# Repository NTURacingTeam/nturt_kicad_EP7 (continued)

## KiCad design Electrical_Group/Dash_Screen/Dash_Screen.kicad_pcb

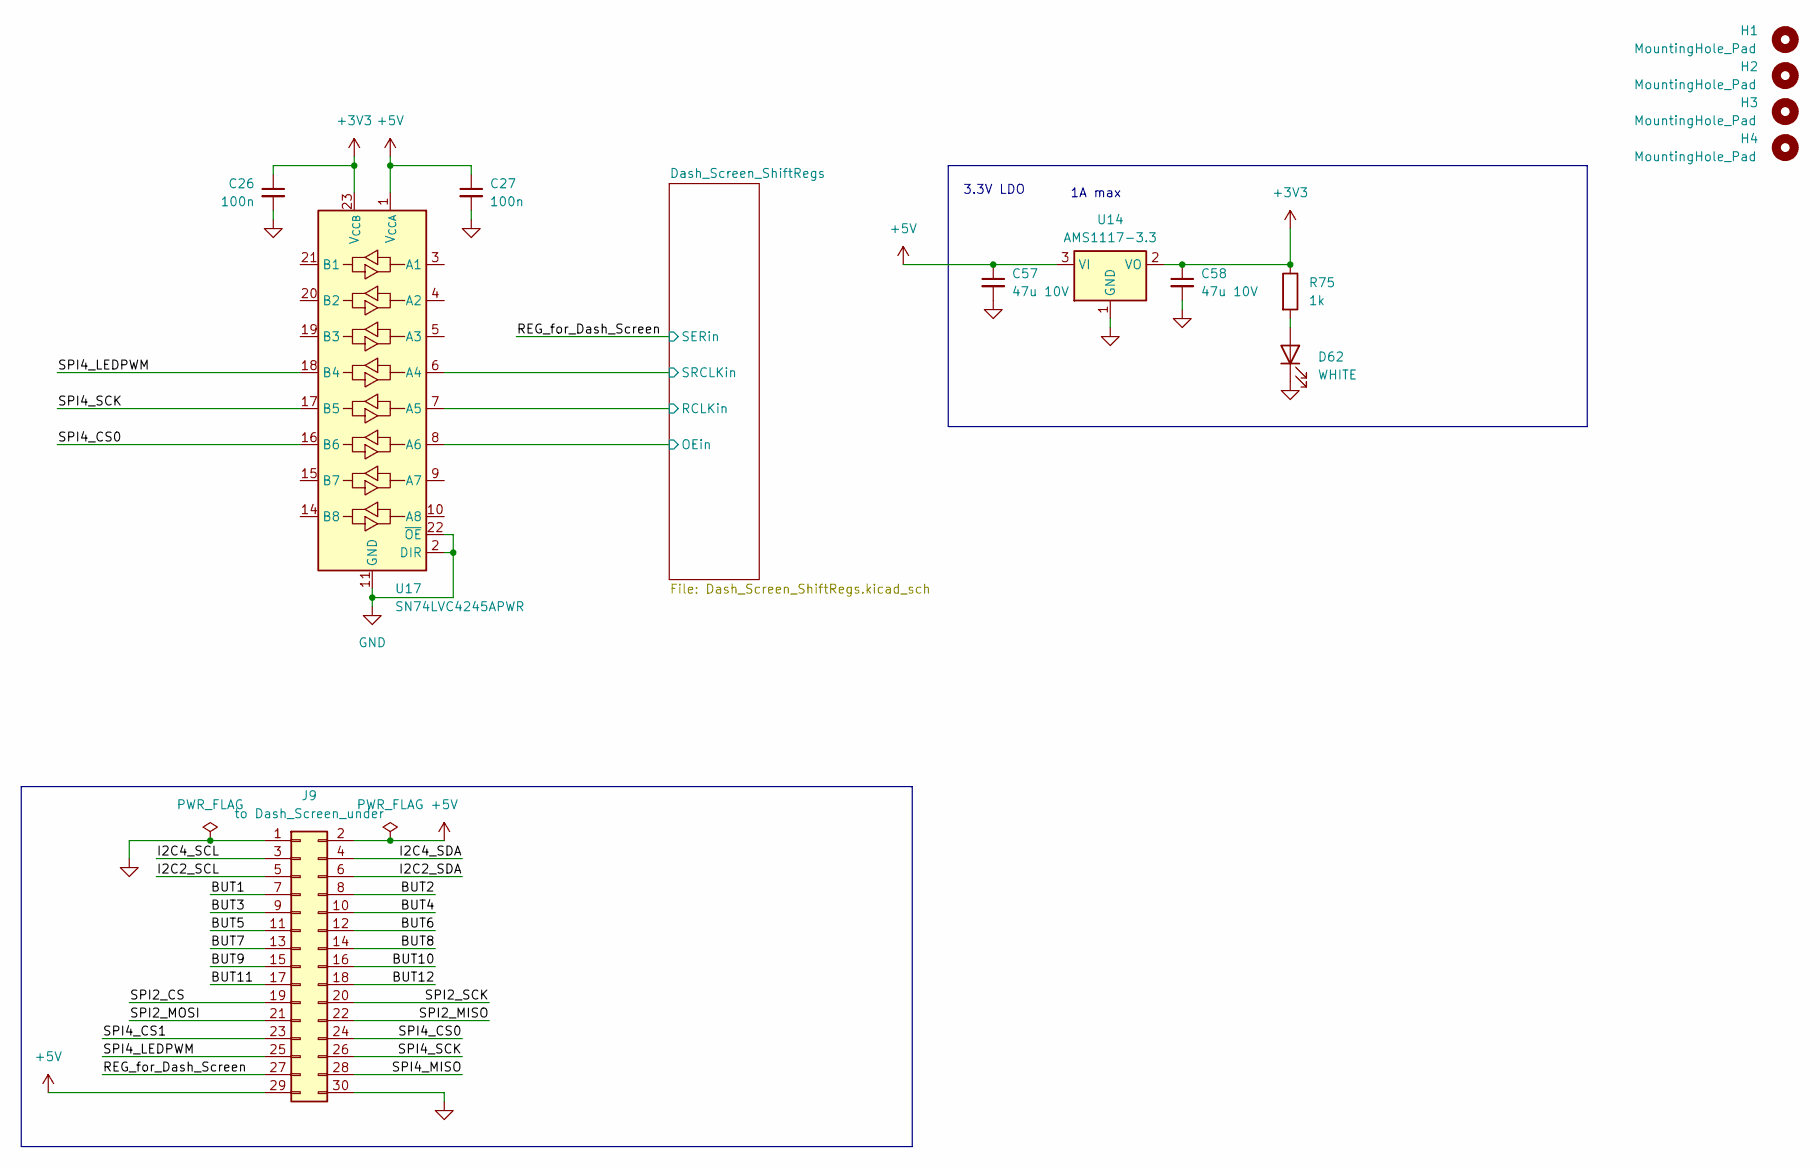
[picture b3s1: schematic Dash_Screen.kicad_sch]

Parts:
C26, C27: 100n; C_0603_1608Metric
C57, C58: 47u 10V; C_1206_3216Metric
D62: WHITE; LED_0603_1608Metric
H1, H2, H3, H4: MountingHole_Pad; MountingHole_3.2mm_M3
J9: to Dash_Screen_under; PinSocket_2x15_P2.00mm_Vertical_SMD
R75: 1k; R_0603_1608Metric
U14: AMS1117-3.3; SOT-223-3_TabPin2
U17: SN74LVC4245APWR; TSSOP-24_4.4x7.8mm_P0.65mm

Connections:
+3V3: C26.1, C58.1, R75.1, U14.2 (VO), U17.23 (V_{CCB}), U17.24 (V_{CCB})
+5V: C27.1, C57.1, J9.2, J9.29, U14.3 (VI), U17.1 (V_{CCA}); also elsewhere on the board
/BUT1: J9.7
/BUT2: J9.8
/BUT3: J9.9
/BUT4: J9.10
/BUT5: J9.11
/BUT6: J9.12
/BUT7: J9.13
/BUT8: J9.14
/BUT9: J9.15
/BUT10: J9.16
/BUT11: J9.17
/BUT12: J9.18
/Dash_Screen_ShiftRegs/OE: U17.8 (A6); also elsewhere on the board
/Dash_Screen_ShiftRegs/RCLK: U17.7 (A5); also elsewhere on the board
/Dash_Screen_ShiftRegs/SRCLK: U17.6 (A4); also elsewhere on the board
/I2C2_SCL: J9.5
/I2C2_SDA: J9.6
/I2C4_SCL: J9.3
/I2C4_SDA: J9.4
/REG_for_Dash_Screen: J9.27; also elsewhere on the board
/SPI2_CS: J9.19
/SPI2_MISO: J9.22
/SPI2_MOSI: J9.21
/SPI2_SCK: J9.20
/SPI4_CS0: J9.24, U17.16 (B6)
/SPI4_CS1: J9.23
/SPI4_LEDPWM: J9.25, U17.18 (B4)
/SPI4_MISO: J9.28
/SPI4_SCK: J9.26, U17.17 (B5)
GND: C26.2, C27.2, C57.2, C58.2, D62.1 (K), J9.1, J9.30, U14.1 (GND), U17.2 (DIR), U17.11 (GND), U17.12 (GND), U17.13 (GND), U17.22 (~OE); also elsewhere on the board
unnamed: D62.2 (A), R75.2

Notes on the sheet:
3.3V LDO
1A max

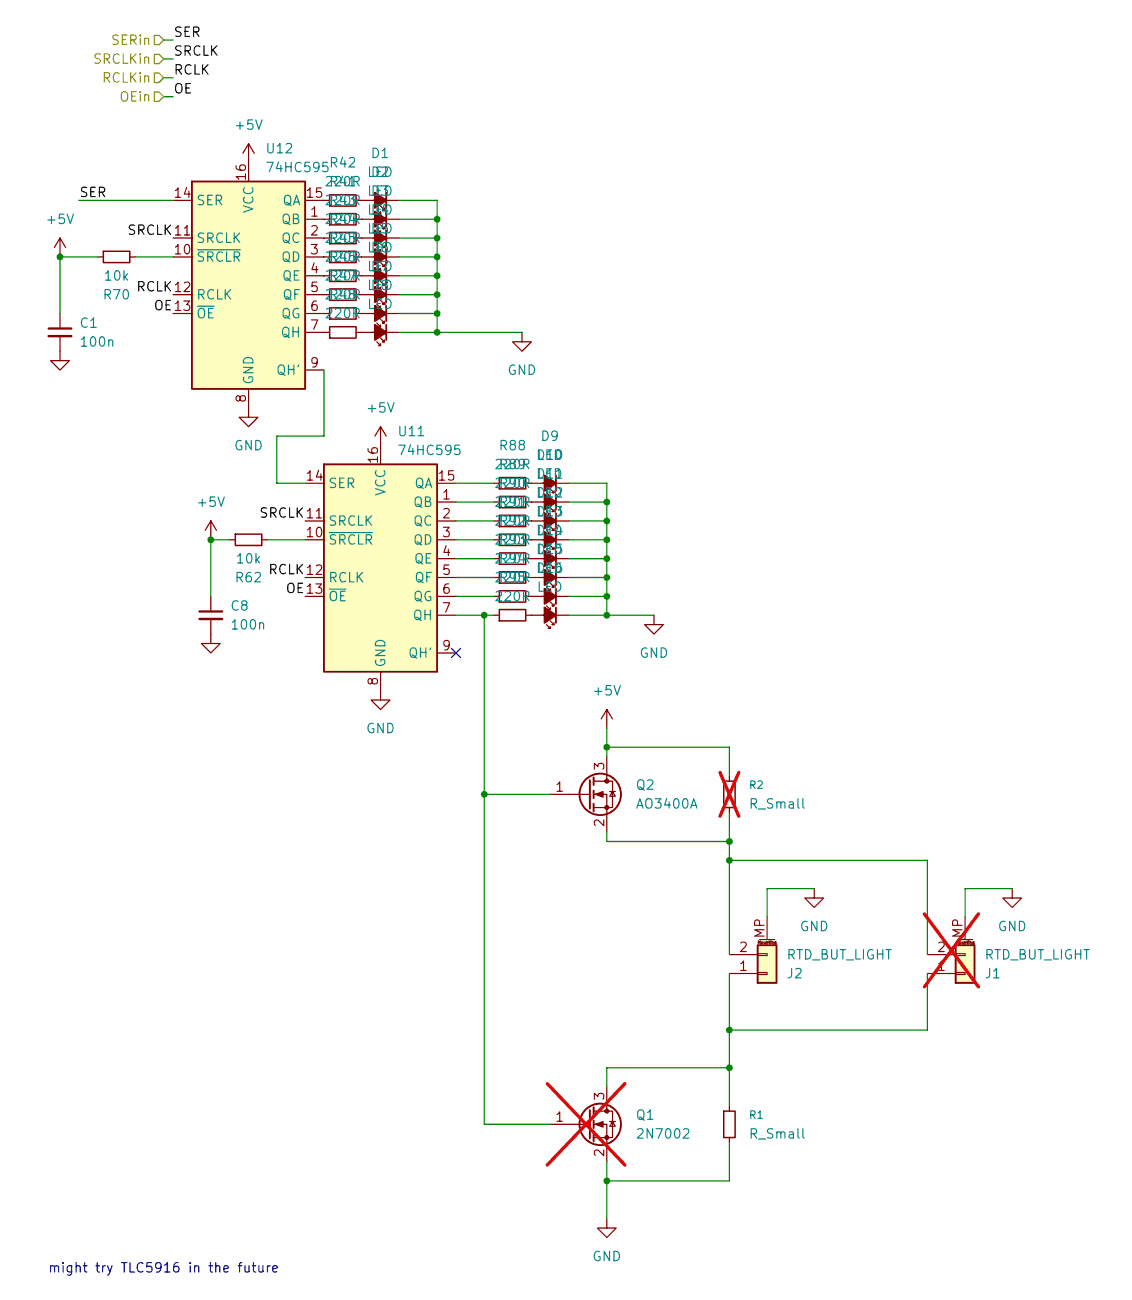
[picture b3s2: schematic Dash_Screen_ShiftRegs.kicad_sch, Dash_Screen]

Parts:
C1, C8: 100n; C_0603_1608Metric
D1, D2, D3, D4, D5, D6, D7, D8, D9, D10, D11, D12, D13, D14, D15, D16: LED; LED_PLCC_2835_Handsoldering
J1: RTD_BUT_LIGHT; JST_PH_S2B-PH-SM4-TB_1x02-1MP_P2.00mm_Horizontal; not fitted
J2: RTD_BUT_LIGHT; JST_PH_S2B-PH-SM4-TB_1x02-1MP_P2.00mm_Horizontal
Q1: 2N7002; SOT-23; not fitted
Q2: AO3400A; SOT-23
R1: R_Small; R_0805_2012Metric_Pad1.20x1.40mm_HandSolder
R2: R_Small; R_0805_2012Metric_Pad1.20x1.40mm_HandSolder; not fitted
R41, R42, R43, R44, R45, R46, R47, R48, R88, R89, R90, R91, R92, R93, R94, R95: 220R; R_0603_1608Metric_Pad0.98x0.95mm_HandSolder
R62, R70: 10k; R_0603_1608Metric
U11, U12: 74HC595; SOIC-16_3.9x9.9mm_P1.27mm

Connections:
+5V: C1.1, C8.1, Q2.3 (D), R2.1, R62.1, R70.1, U11.16 (VCC), U12.16 (VCC); also elsewhere on the board
/Dash_Screen_ShiftRegs/OE: U11.13 (~OE), U12.13 (~OE); also elsewhere on the board
/Dash_Screen_ShiftRegs/RCLK: U11.12 (RCLK), U12.12 (RCLK); also elsewhere on the board
/Dash_Screen_ShiftRegs/SRCLK: U11.11 (SRCLK), U12.11 (SRCLK); also elsewhere on the board
/REG_for_Dash_Screen: U12.14 (SER); also elsewhere on the board
GND: C1.2, C8.2, D1.1 (K), D2.1 (K), D3.1 (K), D4.1 (K), D5.1 (K), D6.1 (K), D7.1 (K), D8.1 (K), D9.1 (K), D10.1 (K), D11.1 (K), D12.1 (K), D13.1 (K), D14.1 (K), D15.1 (K), D16.1 (K), J1.MP (MountPin), J2.MP (MountPin), Q1.2 (S), R1.2, U11.8 (GND), U12.8 (GND); also elsewhere on the board
unnamed: D1.2 (A), R42.2
unnamed: D2.2 (A), R41.2
unnamed: D3.2 (A), R43.2
unnamed: D4.2 (A), R44.2
unnamed: D5.2 (A), R45.2
unnamed: D6.2 (A), R46.2
unnamed: D7.2 (A), R47.2
unnamed: D8.2 (A), R48.2
unnamed: D9.2 (A), R88.2
unnamed: D10.2 (A), R89.2
unnamed: D11.2 (A), R90.2
unnamed: D12.2 (A), R91.2
unnamed: D13.2 (A), R92.2
unnamed: D14.2 (A), R93.2
unnamed: D15.2 (A), R94.2
unnamed: D16.2 (A), R95.2
unnamed: J1.1, J2.1, Q1.3 (D), R1.1
unnamed: J1.2, J2.2, Q2.2 (S), R2.2
unnamed: Q1.1 (G), Q2.1 (G), R95.1, U11.7 (QH)
unnamed: R88.1, U11.15 (QA)
unnamed: R89.1, U11.1 (QB)
unnamed: R90.1, U11.2 (QC)
unnamed: R91.1, U11.3 (QD)
unnamed: R92.1, U11.4 (QE)
unnamed: R93.1, U11.5 (QF)
unnamed: R94.1, U11.6 (QG)
unnamed: U11.14 (SER), U12.9 (QH')
unnamed: R62.2, U11.10 (~SRCLR)
unnamed: R42.1, U12.15 (QA)
unnamed: R41.1, U12.1 (QB)
unnamed: R43.1, U12.2 (QC)
unnamed: R44.1, U12.3 (QD)
unnamed: R45.1, U12.4 (QE)
unnamed: R46.1, U12.5 (QF)
unnamed: R47.1, U12.6 (QG)
unnamed: R48.1, U12.7 (QH)
unnamed: R70.2, U12.10 (~SRCLR)

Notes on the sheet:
might try TLC5916 in the future

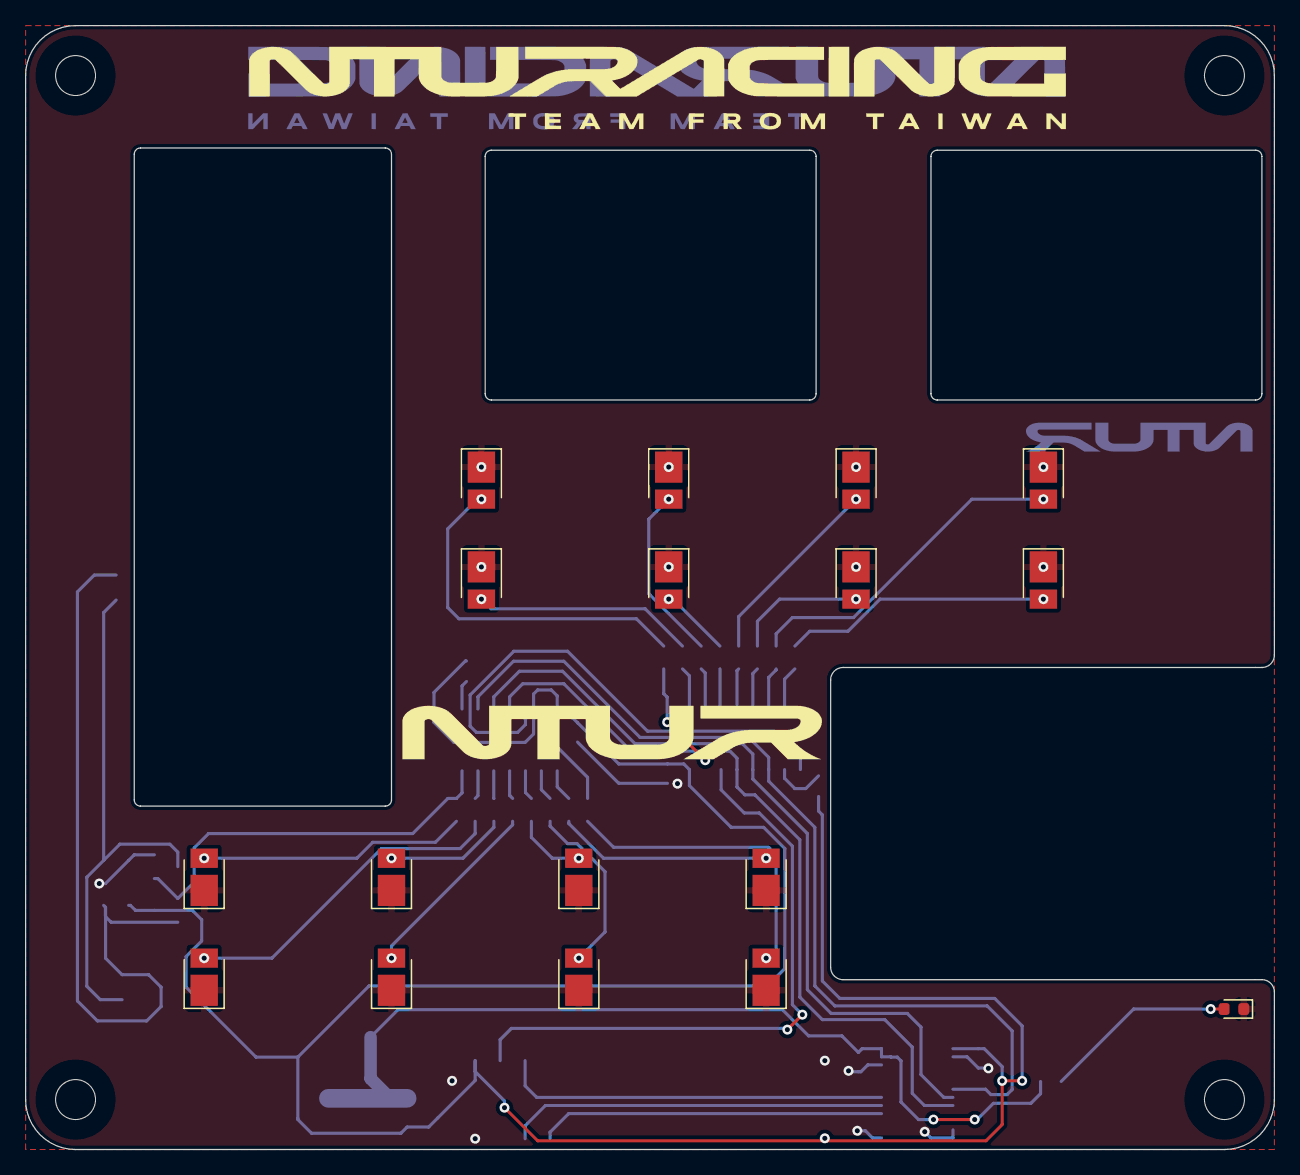
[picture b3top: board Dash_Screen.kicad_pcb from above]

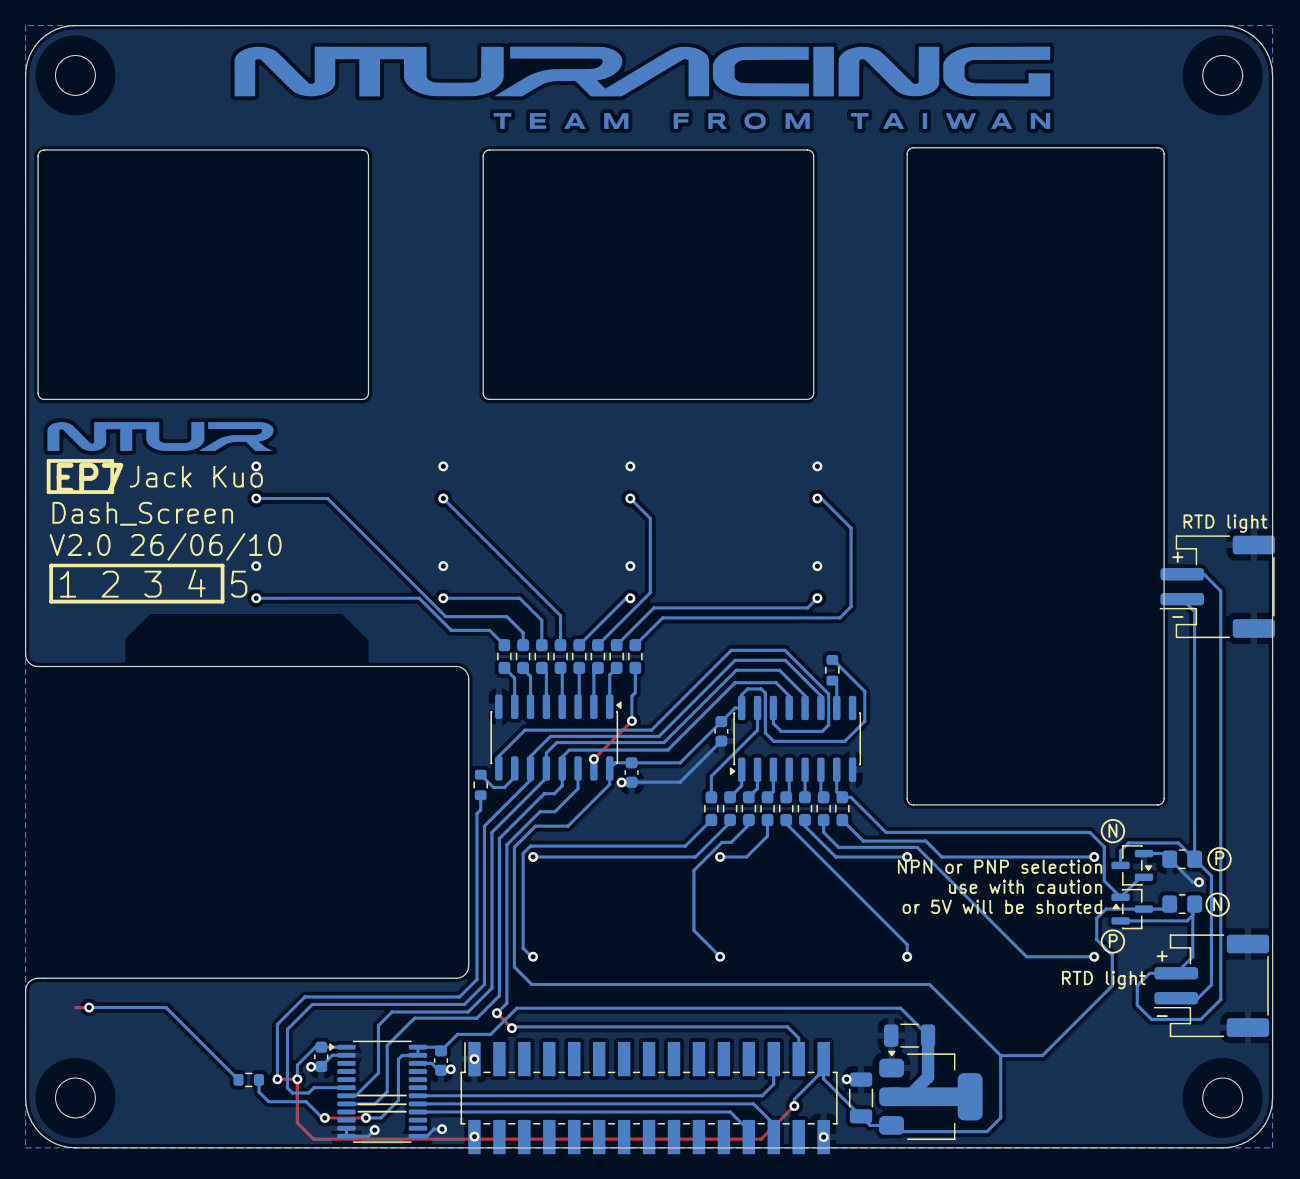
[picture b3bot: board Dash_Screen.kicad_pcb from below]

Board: 2 copper layers, 100.0 x 90.0 mm, 57 parts (36 on the bottom side), 48 nets.

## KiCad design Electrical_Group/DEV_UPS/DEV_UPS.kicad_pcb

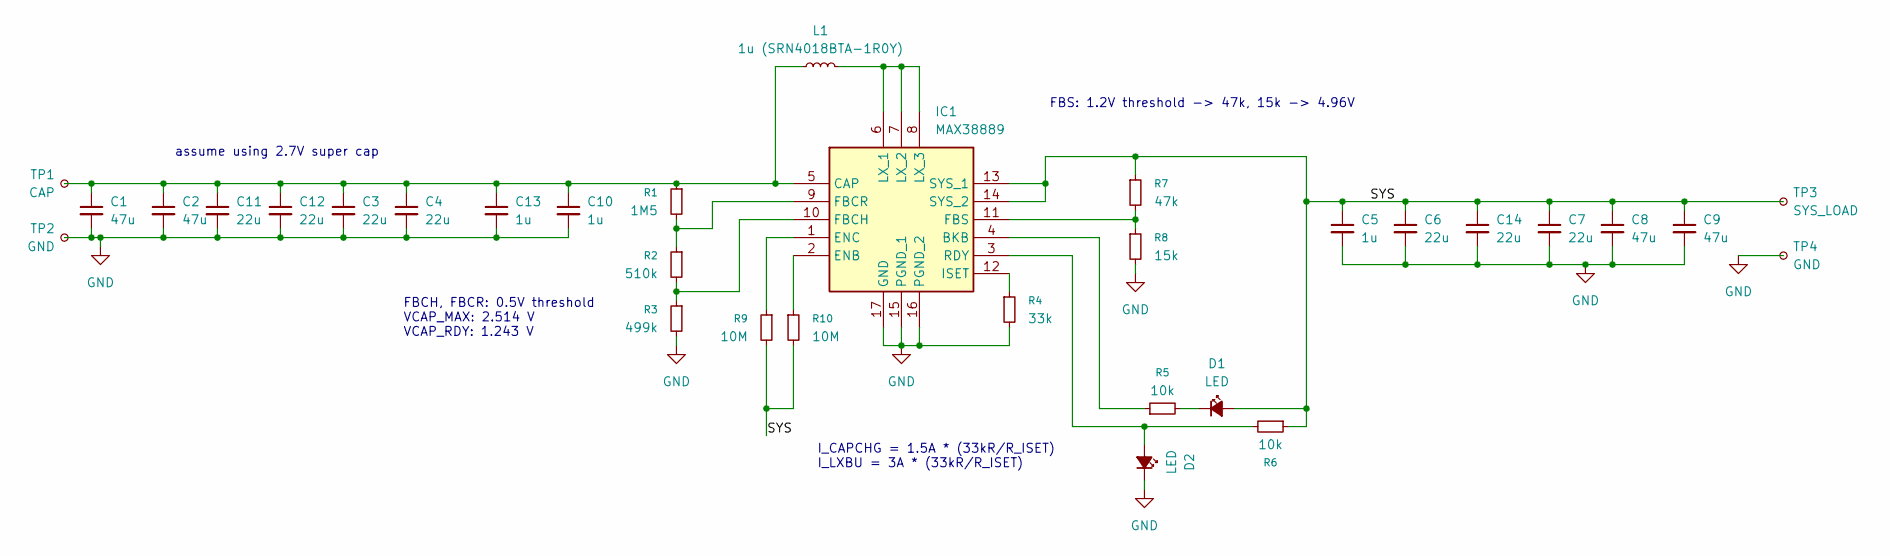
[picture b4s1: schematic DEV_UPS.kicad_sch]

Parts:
C1, C2, C8, C9: 47u; C_1206_3216Metric_Pad1.33x1.80mm_HandSolder
C3, C4, C6, C7, C11, C12, C14: 22u; C_0805_2012Metric_Pad1.18x1.45mm_HandSolder
C5, C10, C13: 1u; C_0603_1608Metric_Pad1.08x0.95mm_HandSolder
D1, D2: LED; LED_0603_1608Metric_Pad1.05x0.95mm_HandSolder
IC1: MAX38889; TQFN-16-1EP_3x3mm_P0.5mm_EP1.6x1.6mm; Mouser Part Number 700-MAX38889AATE+
L1: 1u (SRN4018BTA-1R0Y); L_Bourns-SRN4018
R1: 1M5; R_0603_1608Metric_Pad0.98x0.95mm_HandSolder
R2: 510k; R_0603_1608Metric_Pad0.98x0.95mm_HandSolder
R3: 499k; R_0603_1608Metric_Pad0.98x0.95mm_HandSolder
R4: 33k; R_0603_1608Metric_Pad0.98x0.95mm_HandSolder
R5, R6: 10k; R_0603_1608Metric_Pad0.98x0.95mm_HandSolder
R7: 47k; R_0603_1608Metric_Pad0.98x0.95mm_HandSolder
R8: 15k; R_0603_1608Metric_Pad0.98x0.95mm_HandSolder
R9, R10: 10M; R_0603_1608Metric_Pad0.98x0.95mm_HandSolder
TP1: CAP; edge_pad_1.4mm_0.7mm
TP2, TP4: GND; edge_pad_1.4mm_0.7mm
TP3: SYS_LOAD; edge_pad_1.4mm_0.7mm

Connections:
/SYS: C5.1, C6.1, C7.1, C8.1, C9.1, C14.1, D1.2 (A), IC1.13 (SYS_1), IC1.14 (SYS_2), R6.1, R7.1, R9.2, R10.2, TP3.1
GND: C1.2, C2.2, C3.2, C4.2, C5.2, C6.2, C7.2, C8.2, C9.2, C10.2, C11.2, C12.2, C13.2, C14.2, D2.1 (K), IC1.15 (PGND_1), IC1.16 (PGND_2), IC1.17 (GND), R3.2, R4.2, R8.2, TP2.1, TP4.1
unnamed: D1.1 (K), R5.2
unnamed: D2.2 (A), IC1.3 (RDY), R6.2
unnamed: IC1.4 (BKB), R5.1
unnamed: C1.1, C2.1, C3.1, C4.1, C10.1, C11.1, C12.1, C13.1, IC1.5 (CAP), L1.1, R1.1, TP1.1
unnamed: IC1.2 (ENB), R10.1
unnamed: IC1.1 (ENC), R9.1
unnamed: IC1.10 (FBCH), R2.2, R3.1
unnamed: IC1.9 (FBCR), R1.2, R2.1
unnamed: IC1.11 (FBS), R7.2, R8.1
unnamed: IC1.12 (ISET), R4.1
unnamed: IC1.6 (LX_1), IC1.7 (LX_2), IC1.8 (LX_3), L1.2

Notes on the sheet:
I_CAPCHG = 1.5A * (33kR/R_ISET) I_LXBU = 3A * (33kR/R_ISET)
FBCH, FBCR: 0.5V threshold VCAP_MAX: 2.514 V VCAP_RDY: 1.243 V
assume using 2.7V super cap
FBS: 1.2V threshold -> 47k, 15k -> 4.96V

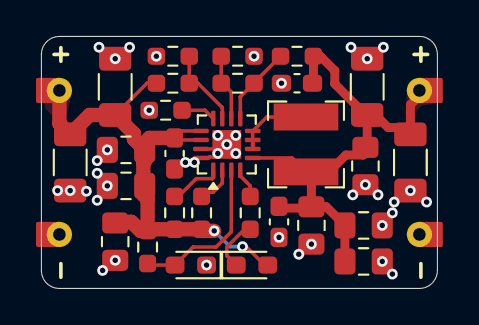
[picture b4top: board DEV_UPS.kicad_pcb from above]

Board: 2 copper layers, 22.0 x 14.0 mm, 32 parts (0 on the bottom side), 13 nets.

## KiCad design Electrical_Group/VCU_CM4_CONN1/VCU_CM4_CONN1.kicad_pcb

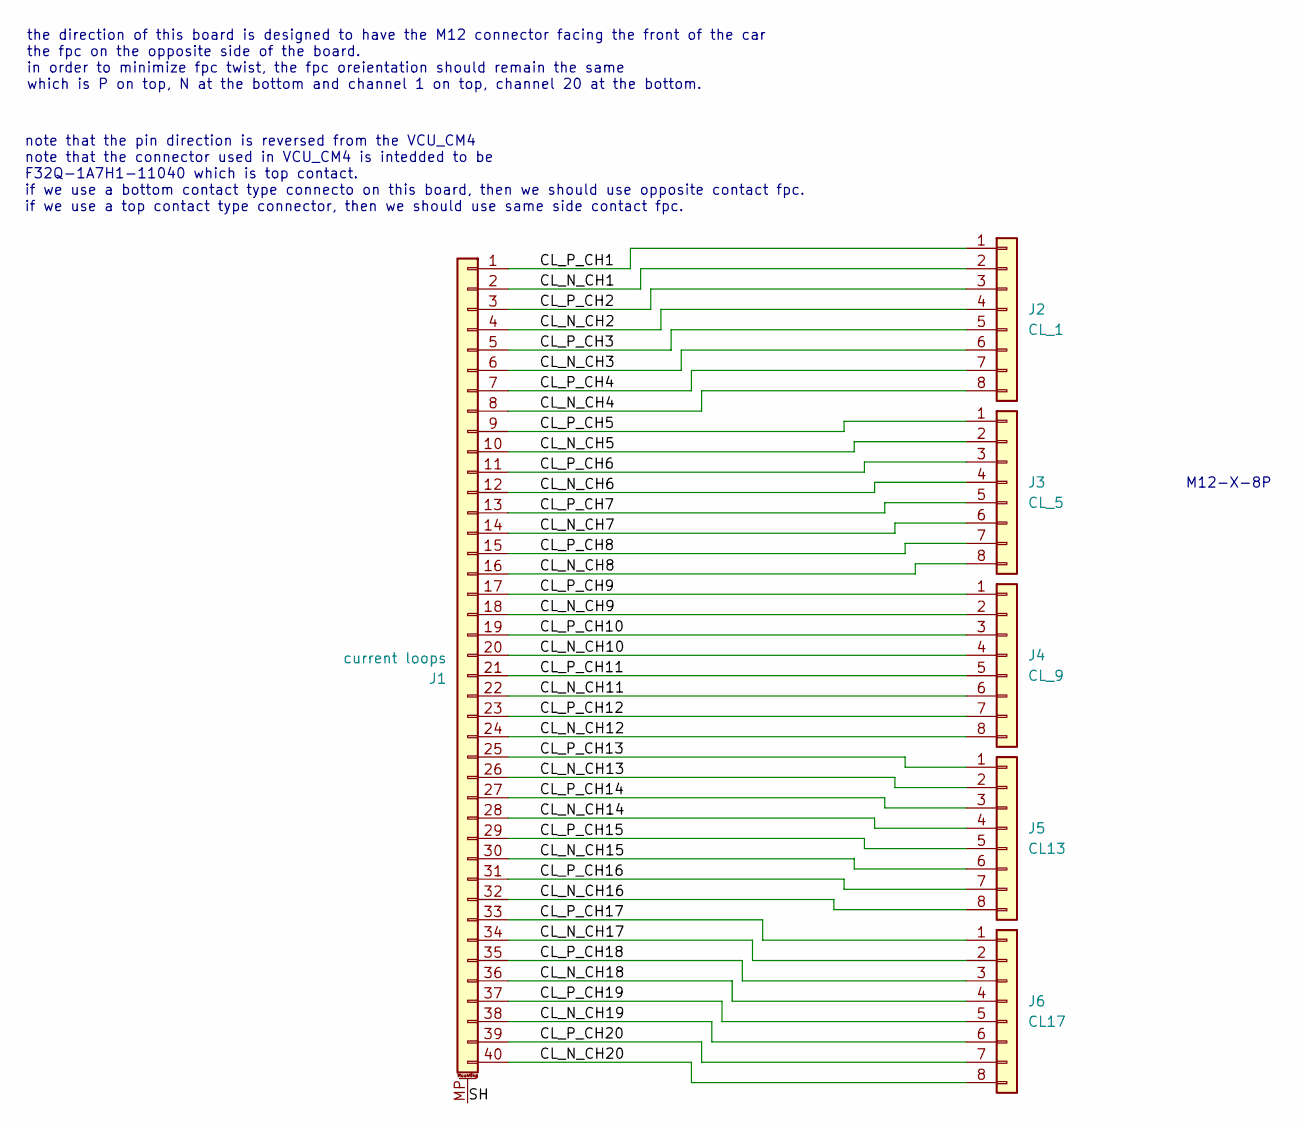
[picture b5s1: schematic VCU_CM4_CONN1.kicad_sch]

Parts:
J1: current loops; TE_4-1734839-0_1x40-1MP_P0.5mm_Horizontal
J2: CL_1; NianYeong-M12-X-F4P
J3: CL_5; NianYeong-M12-X-F4P
J4: CL_9; NianYeong-M12-X-F4P
J5: CL13; NianYeong-M12-X-F4P
J6: CL17; NianYeong-M12-X-F4P

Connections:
/CL_N_CH1: J1.2, J2.2
/CL_N_CH2: J1.4, J2.4
/CL_N_CH3: J1.6, J2.6
/CL_N_CH4: J1.8, J2.8
/CL_N_CH5: J1.10, J3.2
/CL_N_CH6: J1.12, J3.4
/CL_N_CH7: J1.14, J3.6
/CL_N_CH8: J1.16, J3.8
/CL_N_CH9: J1.18, J4.2
/CL_N_CH10: J1.20, J4.4
/CL_N_CH11: J1.22, J4.6
/CL_N_CH12: J1.24, J4.8
/CL_N_CH13: J1.26, J5.2
/CL_N_CH14: J1.28, J5.4
/CL_N_CH15: J1.30, J5.6
/CL_N_CH16: J1.32, J5.8
/CL_N_CH17: J1.34, J6.2
/CL_N_CH18: J1.36, J6.4
/CL_N_CH19: J1.38, J6.6
/CL_N_CH20: J1.40, J6.8
/CL_P_CH1: J1.1, J2.1
/CL_P_CH2: J1.3, J2.3
/CL_P_CH3: J1.5, J2.5
/CL_P_CH4: J1.7, J2.7
/CL_P_CH5: J1.9, J3.1
/CL_P_CH6: J1.11, J3.3
/CL_P_CH7: J1.13, J3.5
/CL_P_CH8: J1.15, J3.7
/CL_P_CH9: J1.17, J4.1
/CL_P_CH10: J1.19, J4.3
/CL_P_CH11: J1.21, J4.5
/CL_P_CH12: J1.23, J4.7
/CL_P_CH13: J1.25, J5.1
/CL_P_CH14: J1.27, J5.3
/CL_P_CH15: J1.29, J5.5
/CL_P_CH16: J1.31, J5.7
/CL_P_CH17: J1.33, J6.1
/CL_P_CH18: J1.35, J6.3
/CL_P_CH19: J1.37, J6.5
/CL_P_CH20: J1.39, J6.7
/SH: J1.MP (MountPin)

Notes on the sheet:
the direction of this board is designed to have the M12 connector facing the front of the car the fpc on the opposite side of the board. in order to minimize fpc twist, the fpc oreientation should remain the same which is P on top, N at the bottom and channel 1 on top, channel 20 at the bottom.
note that the pin direction is reversed from the VCU_CM4 note that the connector used in VCU_CM4 is intedded to be F32Q-1A7H1-11040 which is top contact. if we use a bottom contact type connecto on this board, then we should use opposite contact fpc. if we use a top contact type connector, then we 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
M12-X-8P

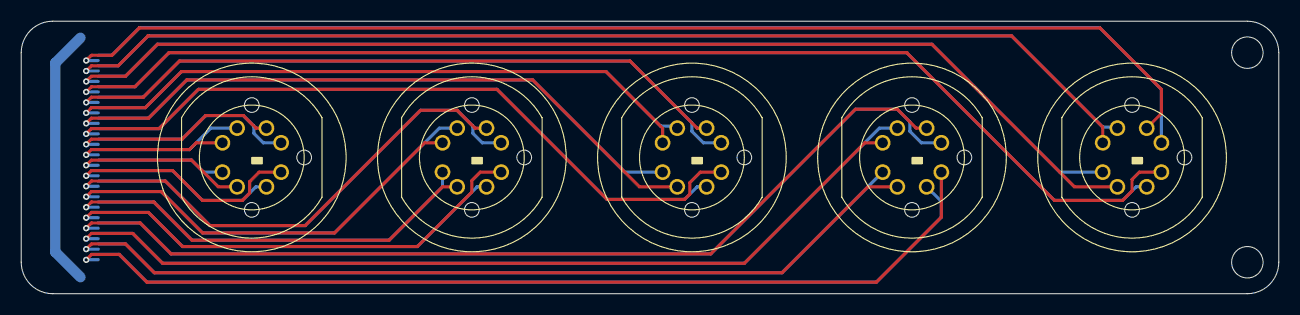
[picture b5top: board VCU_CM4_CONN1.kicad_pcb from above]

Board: 2 copper layers, 120.0 x 26.0 mm, 6 parts (1 on the bottom side), 40 nets.

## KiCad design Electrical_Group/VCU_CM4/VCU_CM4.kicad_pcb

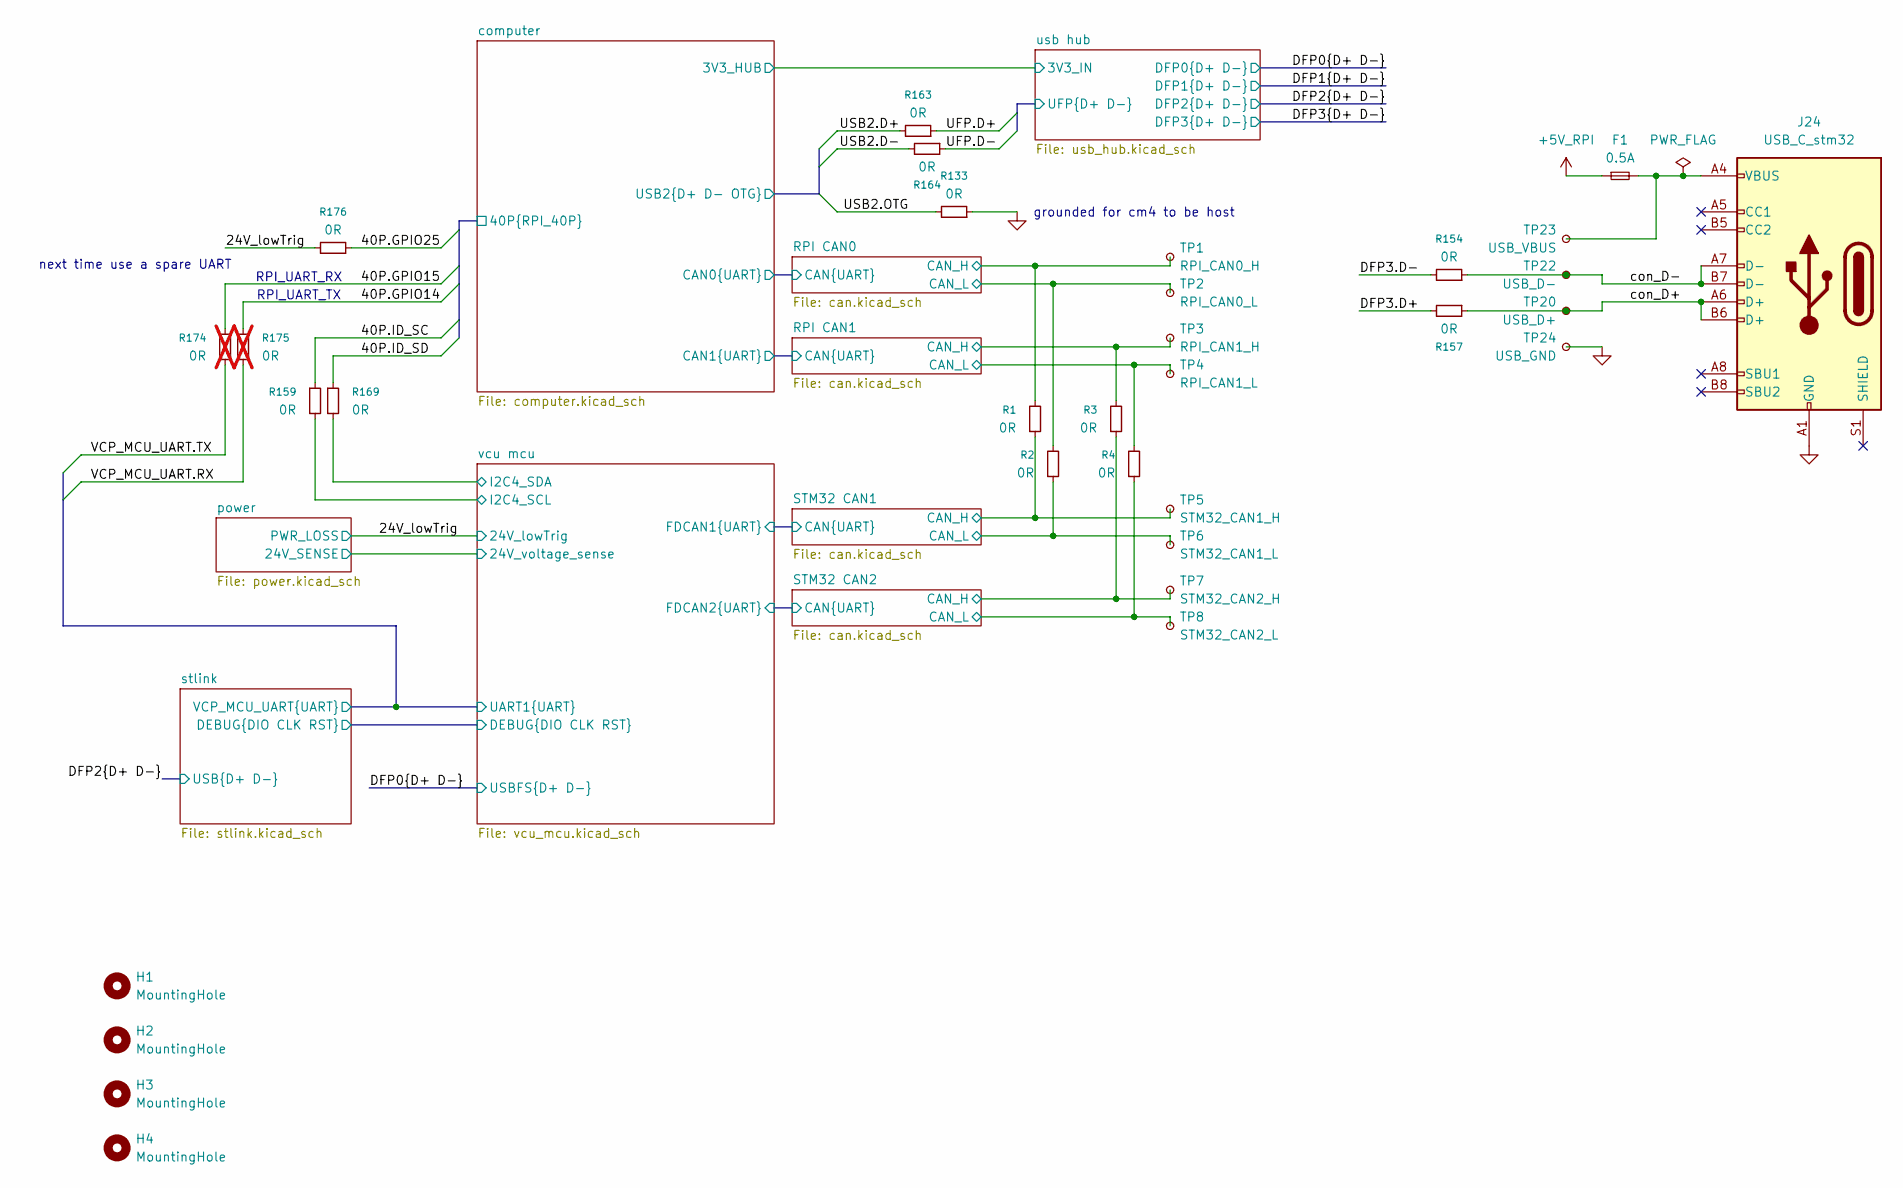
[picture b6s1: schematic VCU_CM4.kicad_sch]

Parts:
F1: 0.5A; Fuse_1206_3216Metric_Pad1.42x1.75mm_HandSolder
H1, H2, H3, H4: MountingHole; MountingHole_3.2mm_M3
J24: USB_C_stm32; USB_C_Receptacle_GCT_USB4105-xx-A_16P_TopMnt_Horizontal
R1, R2, R3, R4, R133, R154, R157, R159, R163, R164, R169, R176: 0R; R_0603_1608Metric_Pad0.98x0.95mm_HandSolder
R174, R175: 0R; R_0603_1608Metric_Pad0.98x0.95mm_HandSolder; not fitted
TP1: RPI_CAN0_H; edge_pad_1.4mm_0.7mm
TP2: RPI_CAN0_L; edge_pad_1.4mm_0.7mm
TP3: RPI_CAN1_H; edge_pad_1.4mm_0.7mm
TP4: RPI_CAN1_L; edge_pad_1.4mm_0.7mm
TP5: STM32_CAN1_H; edge_pad_1.4mm_0.7mm
TP6: STM32_CAN1_L; edge_pad_1.4mm_0.7mm
TP7: STM32_CAN2_H; edge_pad_1.4mm_0.7mm
TP8: STM32_CAN2_L; edge_pad_1.4mm_0.7mm
TP20: USB_D+; TestPoint_Pad_1.5x1.5mm
TP22: USB_D-; TestPoint_Pad_1.5x1.5mm
TP23: USB_VBUS; TestPoint_Pad_1.5x1.5mm
TP24: USB_GND; TestPoint_Pad_1.5x1.5mm

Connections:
+5V_CM: F1.1; also elsewhere on the board
/24V_lowTrig: R176.1; also elsewhere on the board
/DFP3.D+: R157.2; also elsewhere on the board
/DFP3.D-: R154.2; also elsewhere on the board
/RPI CAN0/CAN_H: R1.2, TP1.1; also elsewhere on the board
/RPI CAN0/CAN_L: R2.2, TP2.1; also elsewhere on the board
/RPI CAN1/CAN_H: R3.2, TP3.1; also elsewhere on the board
/RPI CAN1/CAN_L: R4.2, TP4.1; also elsewhere on the board
/STM32 CAN1/CAN_H: R1.1, TP5.1; also elsewhere on the board
/STM32 CAN1/CAN_L: R2.1, TP6.1; also elsewhere on the board
/STM32 CAN2/CAN_H: R3.1, TP7.1; also elsewhere on the board
/STM32 CAN2/CAN_L: R4.1, TP8.1; also elsewhere on the board
/computer/40P.GPIO14: R175.1; also elsewhere on the board
/computer/40P.GPIO15: R174.1; also elsewhere on the board
/computer/40P.GPIO25: R176.2; also elsewhere on the board
/computer/40P.ID_SC: R159.1; also elsewhere on the board
/computer/40P.ID_SD: R169.1; also elsewhere on the board
/computer/USB2.D+: R163.2; also elsewhere on the board
/computer/USB2.D-: R164.2; also elsewhere on the board
/computer/USB2.OTG: R133.2; also elsewhere on the board
/con_D+: J24.A6 (D+), J24.B6 (D+), R157.1, TP20.1
/con_D-: J24.A7 (D-), J24.B7 (D-), R154.1, TP22.1
/stlink/VCP_MCU_UART.RX: R175.2; also elsewhere on the board
/stlink/VCP_MCU_UART.TX: R174.2; also elsewhere on the board
/usb hub/UFP.D+: R163.1; also elsewhere on the board
/usb hub/UFP.D-: R164.1; also elsewhere on the board
/vcu mcu/I2C4_SCL: R159.2; also elsewhere on the board
/vcu mcu/I2C4_SDA: R169.2; also elsewhere on the board
GND: J24.A1 (GND), J24.A12 (GND), J24.B1 (GND), J24.B12 (GND), R133.1, TP24.1; also elsewhere on the board
unnamed: F1.2, J24.A4 (VBUS), J24.A9 (VBUS), J24.B4 (VBUS), J24.B9 (VBUS), TP23.1

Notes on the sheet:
RPI_UART_RX
RPI_UART_TX
next time use a spare UART
grounded for cm4 to be host
